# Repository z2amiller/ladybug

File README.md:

# ladybug
attiny85 + WS2812 replacement for CloudB ladybug nightlight.

## Installation
Album showing disassembly [here](http://imgur.com/a/Ccf88).

The ladybug has six screws that hold the shell on.  They're
under the fabric.  I had to cut a small slit in the fabric to
access some of them, others I was able to get at through
the hole for the battery pack.

## Programming

The ladybug can be programmed in-system with an 8 pin SOIC clip
like [this](http://www.amazon.com/dp/B015W4PKR6).  I have used
a [small programming shield](http://www.electrodragon.com/product/attiny-1385-programming-shield/)
plus an Arduino UNO as the programmer.   You could also make
a custom cable to hook onto a dedicated programmer like the
[USBASP](http://www.electrodragon.com/product/8051-avr-mcu-programmer-usbasp/)
programmer.

## Future work

It turns out that the WS2812b LEDs (aka Neopixels) have quite a high
quiescent current - around 800uA.  This ends up eating batteries
moderately quickly.

One idea would be to connect the wakeup button to a
[soft latching circuit](http://electronics.stackexchange.com/questions/4060/make-a-momentary-switch-control-a-toggle)
and use the output of the toggle control the enable pin of a power
regulator end connect the current WAKE pin on the attiny85 as a
second momentary input to turn it off after 30 minutes.

For example, that circuit controlling the enable pin of a 5V boost
regulator would make the following improvements:

* Vastly reduced quiescent current, probably under 20ua.  Only the
  latch would be consuming measureable power.
* Simplified programming, less need for fancy interrupt and sleep
  routines - at the end of the cycle, the attiny85 would just
  poke the toggle and turn the power off.
* Better performance with low batteries.  Right now, as the batteries
  decay, the ladybug gets wonky.  The blue LED has a higher forward
  voltage, so as the batteries start to run down, the blue LED inside
  the WS2818b will no longer light up, though the green and red channels
  continue to work.
* Probably a little bit brighter running at full 5v instead of the 4.5v
  or less coming from 3xAAA batteries.

There is plenty of room on the board for a boost regulator and toggle circuit.

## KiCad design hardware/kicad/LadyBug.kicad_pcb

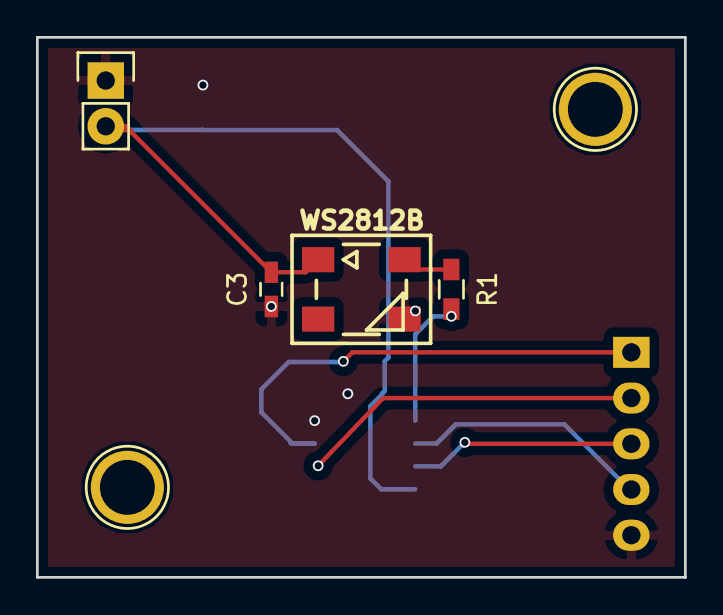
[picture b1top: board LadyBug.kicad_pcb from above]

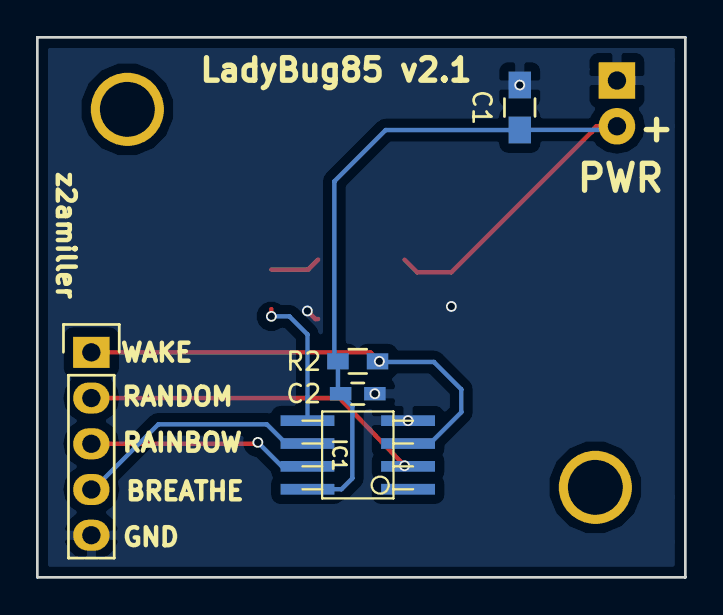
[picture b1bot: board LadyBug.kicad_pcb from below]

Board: 2 copper layers, 36.0 x 30.0 mm, 9 parts (5 on the bottom side), 8 nets.

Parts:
C1: 10uF; C_0805_HandSoldering
C2, C3: 100nf; C_0603_HandSoldering
IC1: ATTINY85-S; so-8
P1: CONN_5; Pin_Header_Straight_1x05
P2: CONN_2; Pin_Header_Straight_1x02
R1: 100; R_0603_HandSoldering
R2: 470K; R_0603_HandSoldering
U1: WS2812B; WS2812b

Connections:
+5V: C1.1, C2.1, C3.2, IC1.8, P2.2, R2.1, U1.1
GND: C1.2, C2.2, C3.1, IC1.4, P1.5, P2.1, U1.3
unnamed: IC1.2, P1.2
unnamed: IC1.3, P1.1, R2.2
unnamed: IC1.5, R1.1
unnamed: IC1.6, P1.4
unnamed: IC1.7, P1.3
unnamed: R1.2, U1.4

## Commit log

2015-10-17 Add MIT license.
2015-10-17 Add the ladybug arduino files.
2015-10-17 Add eagle files for the ladybug.
2015-10-25 Move sketch to make adruino software happy.
2015-10-25 Kicad version of ladybug hardware.
2015-10-25 Add the plotted gerber files.
2015-10-25 Oops, swapped front and back.
2015-10-25 Moved some silscreens around.
2015-10-25 Removed extra gerber zip.
2015-10-25 New gerbers, off to OshPark
2015-11-08 Some ladybug tweaking, v1 of board DOA.
2015-11-08 Added some more silkscreening.
2015-11-08 Changed silkscreen to match version 2.1.
2015-11-08 Add gerber files - off to OshPark again.
2016-05-15 Clean up some whitespace.
2016-05-15 Improved README.
2016-05-19 Better README
